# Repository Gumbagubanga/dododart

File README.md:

# DodoDart - A DIY electronic dart board

This project implements electronic dart board with several games.

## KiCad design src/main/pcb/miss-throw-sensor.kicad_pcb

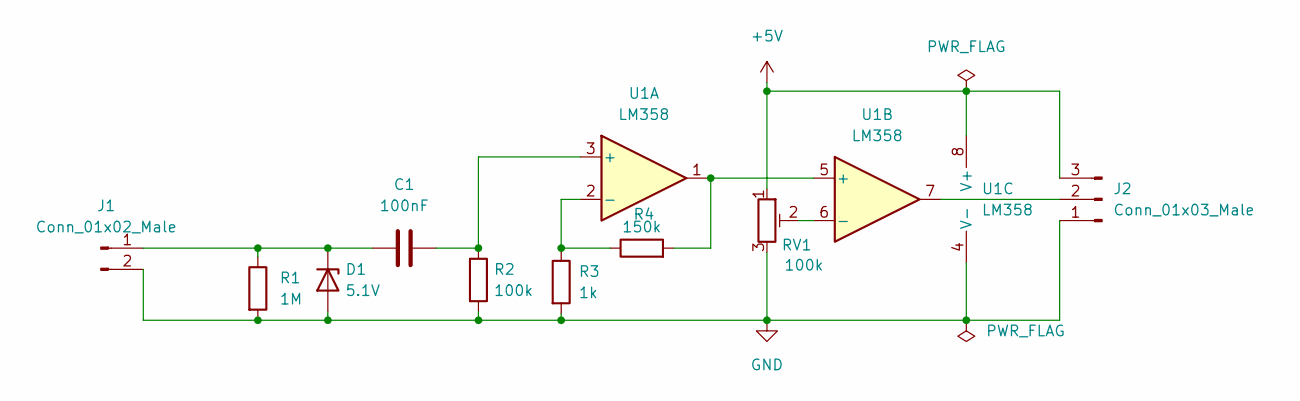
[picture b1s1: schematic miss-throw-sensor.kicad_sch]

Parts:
C1: 100nF; C_Disc_D5.0mm_W2.5mm_P5.00mm
D1: 5.1V; D_DO-35_SOD27_P2.54mm_Vertical_AnodeUp
J1: Conn_01x02_Male; PinHeader_1x02_P2.54mm_Horizontal
J2: Conn_01x03_Male; PinHeader_1x03_P2.54mm_Horizontal
R1: 1M; R_Axial_DIN0207_L6.3mm_D2.5mm_P2.54mm_Vertical
R2: 100k; R_Axial_DIN0207_L6.3mm_D2.5mm_P2.54mm_Vertical
R3: 1k; R_Axial_DIN0207_L6.3mm_D2.5mm_P2.54mm_Vertical
R4: 150k; R_Axial_DIN0207_L6.3mm_D2.5mm_P2.54mm_Vertical
RV1: 100k; Potentiometer_Piher_PT-10-V10_Vertical
U1: LM358; DIP-8_W7.62mm

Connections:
+5V: J2.3, RV1.1, U1.8 (V+)
GND: D1.2 (A), J1.2, J2.1, R1.2, R2.2, R3.2, RV1.3, U1.4 (V-)
unnamed: C1.1, D1.1 (K), J1.1, R1.1
unnamed: C1.2, R2.1, U1.3 (+)
unnamed: J2.2, U1.7
unnamed: R3.1, R4.1, U1.2 (-)
unnamed: R4.2, U1.1, U1.5 (+)
unnamed: RV1.2, U1.6 (-)

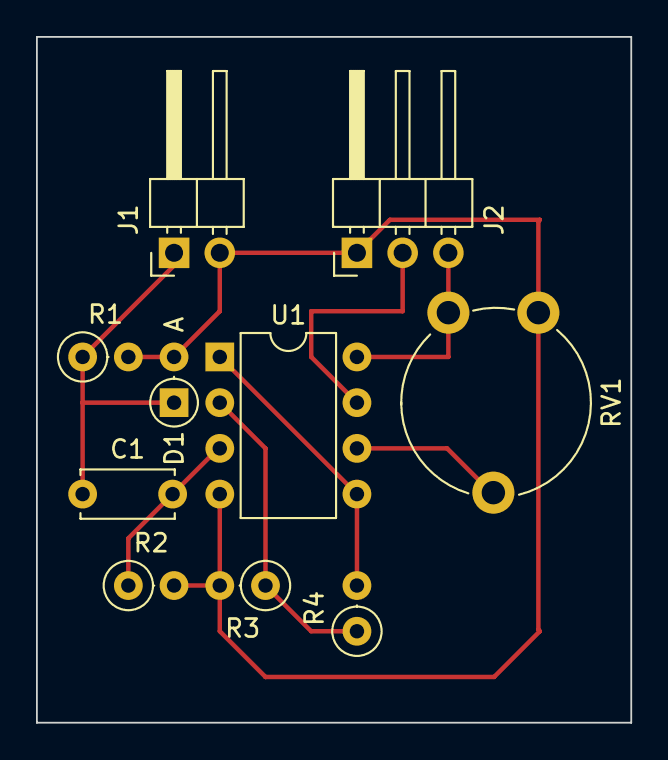
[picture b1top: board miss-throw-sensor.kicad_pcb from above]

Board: 2 copper layers, 33.0 x 38.1 mm, 10 parts (0 on the bottom side), 8 nets.

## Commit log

2023-08-28 301 Elimination implementiert
2023-08-28 Fehlwurfsensor-Schemata und PCB-Footprints hinzugefügt
2023-08-28 Maximale Rundenanzahl in die Rules-Klasse verschoben
2023-08-28 Vollbildmodus implementiert
2023-08-28 HowlerJS und Beispiel hinzugefügt
2023-08-28 Refactoring
2023-08-28 Refactoring und SplitScoreRegeln eingefügt
2023-08-28 Minimination Regeln eingefügt
2023-08-28 SerialPort Refactoring
2023-08-28 Updated .gitignore
2023-08-28 Arduino Code
2023-08-28 Cricket Regeln eingefügt
2023-08-28 501 implementiert
2023-08-28 Regeln als Domänenobjekt eingeführt
2023-08-28 Blinkende Buttons implementiert
2023-08-28 Rendering von der GameEngine getrennt
2023-08-28 Spring Banner deaktiviert
2023-08-28 SerialPort-Handling in eigenes Infrastructure-Subpackage verschoben
2023-08-28 Material Components Web für das Hauptmenü eingeführt
2023-08-28 Soundausgabe implementiert
2023-08-28 Refactoring Abstract
2023-08-28 Maven Dependencies aktualisiert
2023-08-28 Editorconfig hinzugefügt
2023-08-28 Migration von SpringBoot 2 auf 3
2023-08-28 SSE-Handling in eigene Infrastructure-Klasse verschoben
2023-08-28 Material Components Web für das Debug-Menü eingeführt
2023-08-28 NPE in SerialPortDriver gefixt
2023-08-28 README.md added
2023-08-29 Fixed formatting
2023-08-29 Added a basic screen handling
2023-08-31 Updated htmx depedency
2023-08-31 Reworked links on the main menu
2023-08-31 Removed manually added loop flag
2023-08-31 Removed passing domain events to the sse rendering call
2023-08-31 First draft for screen handling
2023-08-31 Reworked the package structure for events and rules
2023-08-31 Reworked the loop and sound sample playback
2023-09-03 Removed debugging code from JS
2023-09-03 Added installation guide for raspberry pi
2023-09-03 Added Highscore rules
2023-09-03 Hide Debug-Button depending on the spring profile
2023-09-06 Switched index back to remote menu page for less confusion
2023-09-07 Added serial connection information for better debugging
2023-09-07 Minor refactoring of serial driver
2023-10-05 Reworked UI
2023-10-05 Improved SSE Driver robustness
2023-10-05 Added automatic switch to Title screen after idle or game over
2023-10-05 Reduced method visibility in Game
2023-10-05 MavenWrapper update
2023-10-05 Updates Spring Boot to 3.1.4
2023-10-06 Fixed bug in sound playback
2023-10-06 Removed distracting background music from game screen
2023-10-06 Replaced soundsprites with more epic sounds
2024-01-27 Updated Spring Version to 3.2.2
